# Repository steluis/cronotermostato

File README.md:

# cronotermostato
Cronotermostato con display touch Nextion 3,2" su placca Vimar Eikon.

Fare riferimeno alla pagina Wiki per dettagli sul funzionamento.

Questo branch serve per rivedere un baco relativo alla grafica di programmazione settimanale del cronotermostato

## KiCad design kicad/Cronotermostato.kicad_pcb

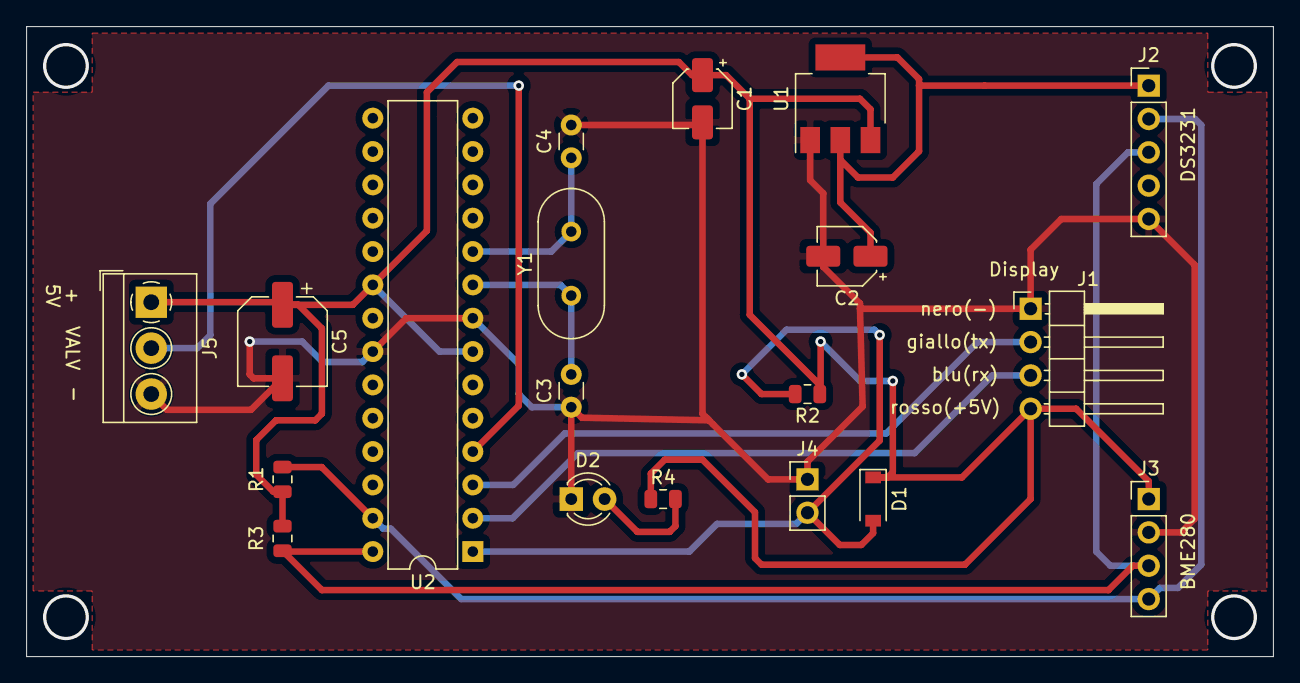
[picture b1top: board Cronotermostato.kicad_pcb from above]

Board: 2 copper layers, 95.0 x 48.0 mm, 19 parts (0 on the bottom side), 12 nets.

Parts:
C1: 10uf; CP_Elec_4x5.3
C2: 10uf; CP_Elec_4x4.5
C3, C4: 22pf; C_Disc_D3.0mm_W1.6mm_P2.50mm
C5: 100uf; CP_Elec_6.3x9.9
D1: 1N4148; D_SOD-123
D2: LED; LED_D3.0mm
J1: Display; PinHeader_1x04_P2.54mm_Horizontal
J2: DS3231; PinHeader_1x05_P2.54mm_Vertical
J3: BME280; PinHeader_1x04_P2.54mm_Vertical
J4: RST; PinHeader_1x02_P2.54mm_Vertical
J5: MainConn; TerminalBlock_4Ucon_1x03_P3.50mm_Horizontal
R1, R2, R3, R4: 220; R_0805_2012Metric
U1: AMS1117; SOT-223-3_TabPin2
U2: ATmega328-PU; DIP-28_W7.62mm
Y1: Crystal; Crystal_HC49-4H_Vertical

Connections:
+3V3: C2.1, J2.1, U1.2
+5V: C1.1, C5.1, D1.1, J1.4, J3.1, J5.1, R1.2, R2.1, R3.2, R4.1, U1.3, U2.7, U2.20
/RX: J1.3, U2.2
/SCL: J2.3, J3.3, R3.1, U2.28
/SDA: J2.2, J3.4, R1.1, U2.27
/TX: J1.2, U2.3
/VA: J5.2, U2.4
GND: C1.2, C2.2, C3.1, C4.2, C5.2, D2.1, J1.1, J2.5, J3.2, J4.1, J5.3, U1.1, U2.8, U2.22
unnamed: C3.2, U2.9, Y1.1
unnamed: C4.1, U2.10, Y1.2
unnamed: D1.2, J4.2, R2.2, U2.1
unnamed: D2.2, R4.2

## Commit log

2020-03-16 Create .gitkeep
    Kicad file
2020-03-16 Create .gitkeep
    File gerber
2020-03-24 Aggiornamento del readme file
    Inserito il motivo di questo branch
